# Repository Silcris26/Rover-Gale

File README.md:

# Rover-Gale

A lo largo de los años, la exploración de Marte ha sido un desafío debido a las condiciones inhóspitas y la lejanía del planeta, las misiones tripuladas aún son extremadamente costosas y peligrosas, aún más cuando hablamos del análisis de la corteza marciana, lo que limita la capacidad de intervención humana para llevar a cabo investigaciones directas en su superficie. Esta problemática requiere de soluciones tecnológicas capaces de explorar, analizar y transmitir información desde Marte, la manera más práctica de hacerlo es a través de un Rover fácil de controlar y capaz de explorar el terreno hostil, lugares de complicado alcance y recorrer largas distancias. Se propone la implementación de motorreductores para las llantas traseras y un servomotor capaz de dar la dirección en las llantas delanteras con piezas impresas en 3D para su fácil replicación y reemplazo en caso de averías, su fuente de energía se da a través de baterías recargables lo cual no solo prolonga la vida útil del vehículo sino que también reduce significativamente la contaminación emitida, como resultado tenemos un Rover cuyas características le hacen eficiente, impulsando la comprensión científica y la preparación para misiones humanas en Marte, validado mediante pruebas hechas en terrenos similares.

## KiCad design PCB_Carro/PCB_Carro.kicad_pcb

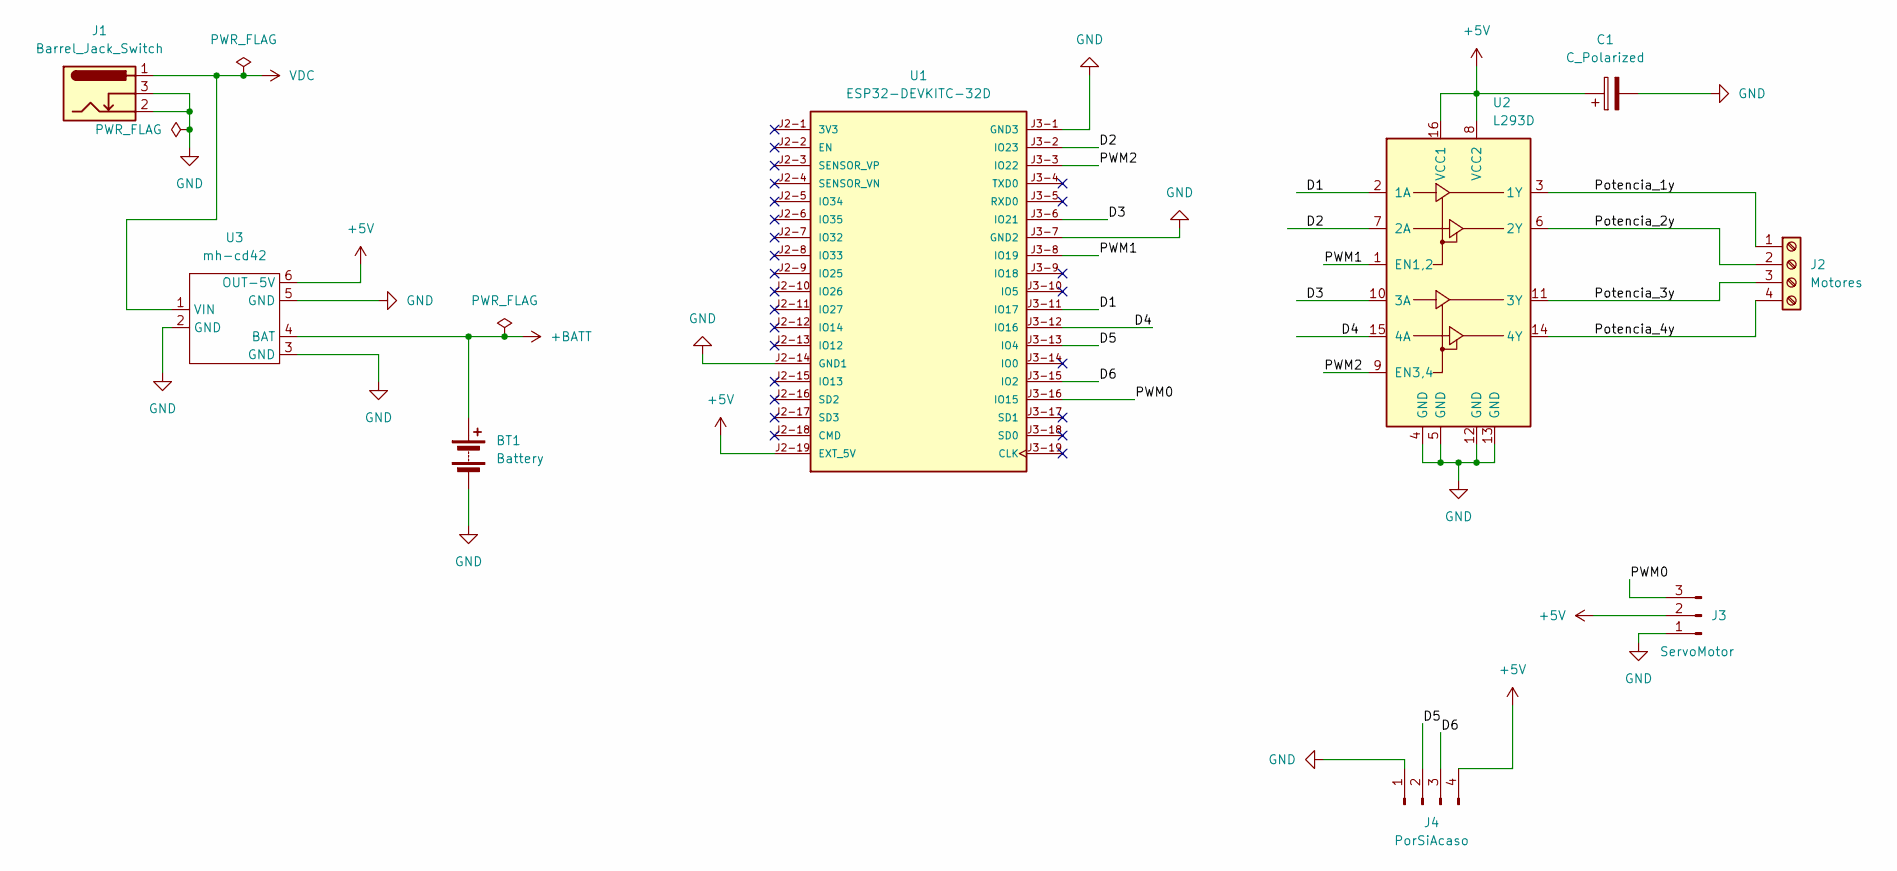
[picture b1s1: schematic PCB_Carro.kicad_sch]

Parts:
BT1: Battery; BatteryHolder_Keystone_1042_1x18650
C1: C_Polarized; CP_Radial_D5.0mm_P2.00mm
J1: Barrel_Jack_Switch; BarrelJack_Horizontal
J2: Motores; TerminalBlock_bornier-4_P5.08mm
J3: ServoMotor; PinHeader_1x03_P2.54mm_Vertical
J4: PorSiAcaso; PinHeader_1x04_P2.54mm_Vertical
U1: ESP32-DEVKITC-32D; MODULE_ESP32-DEVKITC-32D; PARTREV V4; DigiKey_Part_Number 4166-ESP32-DEVKITC-32D-ND
U2: L293D; DIP-16_W7.62mm
U3: mh-cd42

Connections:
+5V: C1.1, J3.2, J4.4, U1.J2-19 (EXT_5V), U2.8 (VCC2), U2.16 (VCC1), U3.6 (OUT-5V)
+BATT: BT1.1 (+), U3.4 (BAT)
/D1: U1.J3-11 (IO17), U2.2 (1A)
/D2: U1.J3-2 (IO23), U2.7 (2A)
/D3: U1.J3-6 (IO21), U2.10 (3A)
/D4: U1.J3-12 (IO16), U2.15 (4A)
/D5: J4.2, U1.J3-13 (IO4)
/D6: J4.3, U1.J3-15 (IO2)
/PWM0: J3.3, U1.J3-16 (IO15)
/PWM1: U1.J3-8 (IO19), U2.1 (EN1,2)
/PWM2: U1.J3-3 (IO22), U2.9 (EN3,4)
/Potencia_1y: J2.1, U2.3 (1Y)
/Potencia_2y: J2.2, U2.6 (2Y)
/Potencia_3y: J2.3, U2.11 (3Y)
/Potencia_4y: J2.4, U2.14 (4Y)
GND: BT1.2 (-), C1.2, J1.2, J1.3, J3.1, J4.1, U1.J2-14 (GND1), U1.J3-1 (GND3), U1.J3-7 (GND2), U2.4 (GND), U2.5 (GND), U2.12 (GND), U2.13 (GND), U3.2 (GND), U3.3 (GND), U3.5 (GND)
VDC: J1.1, U3.1 (VIN)

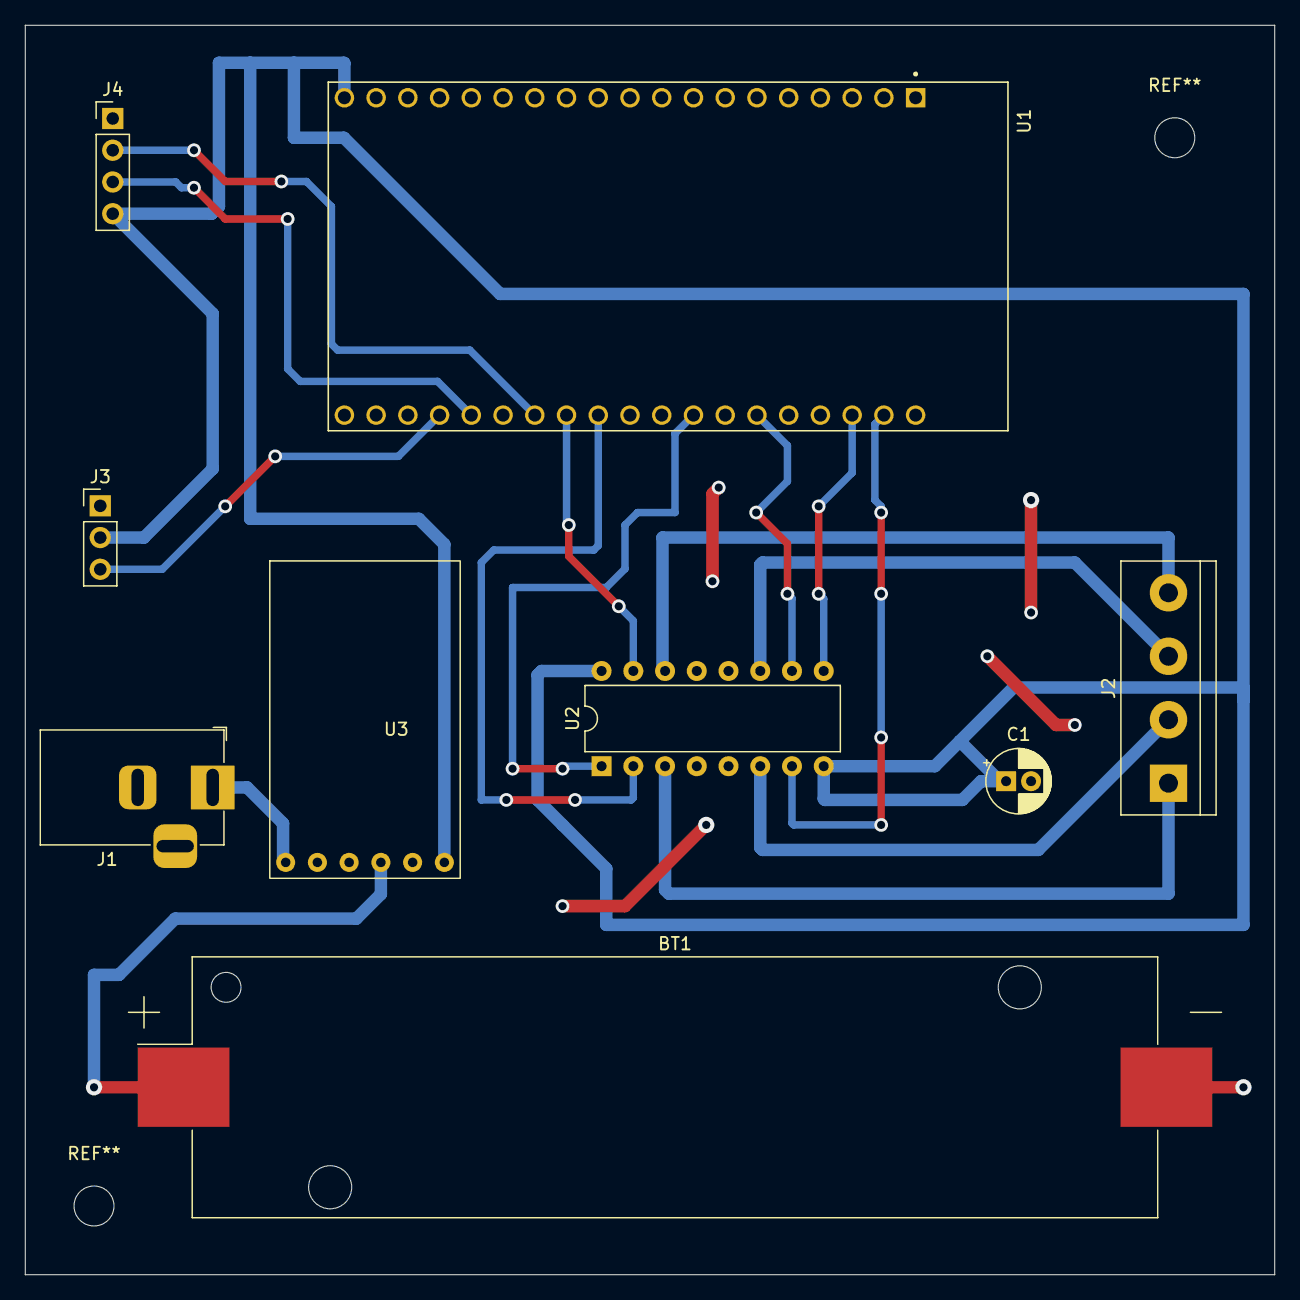
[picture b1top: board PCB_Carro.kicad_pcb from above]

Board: 2 copper layers, 100.0 x 100.0 mm, 9 parts (0 on the bottom side), 17 nets.

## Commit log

2024-09-17 Actualización códigos
2024-09-25 poster
2024-09-25 General
2024-09-25 Actualización imagenes
